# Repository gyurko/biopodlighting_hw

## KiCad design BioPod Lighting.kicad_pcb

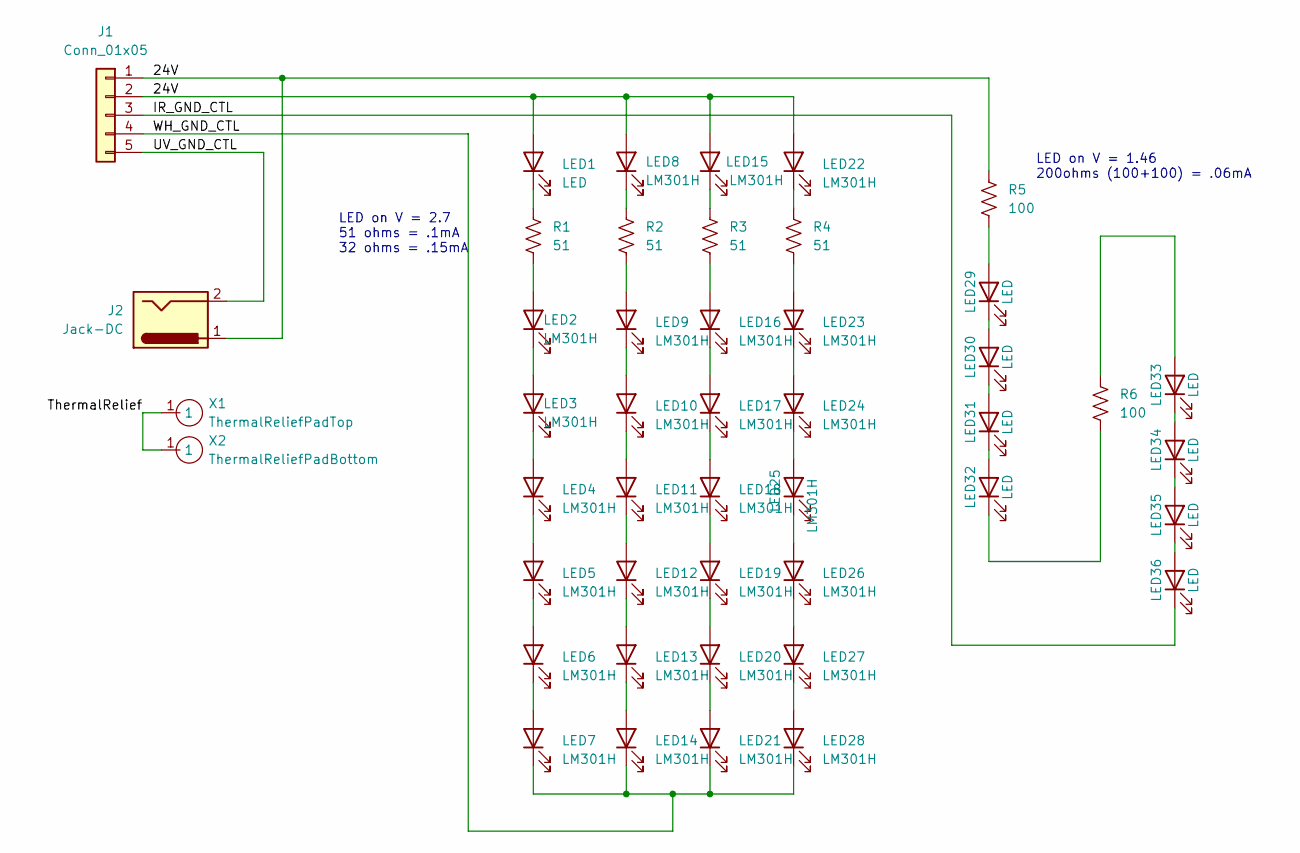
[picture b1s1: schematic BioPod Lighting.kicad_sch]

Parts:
J1: Conn_01x05; 5PinLightConnector
J2: Jack-DC; DisplayBoardDCJack
LED1: LED; LM301H_LED
LED2, LED3, LED4, LED5, LED6, LED7, LED8, LED9, LED10, LED11, LED12, LED13, LED14, LED15, LED16, LED17, LED18, LED19, LED20, LED21, LED22, LED23, LED24, LED25, LED26, LED27, LED28: LM301H; LM301H_LED
LED29, LED30, LED31, LED32, LED33, LED34, LED35, LED36: LED; SFH-4258_LED
R1, R2, R3, R4: 51; R_2512_6332Metric_Pad1.40x3.35mm_HandSolder
R5, R6: 100; R_2512_6332Metric_Pad1.40x3.35mm_HandSolder
X1: ThermalReliefPadTop; ThermalReliefWithMask
X2: ThermalReliefPadBottom; ThermalReliefNoMask

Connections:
/24V: J1.1, J1.2, J2.1, LED1.2 (A), LED8.2 (A), LED15.2 (A), LED22.2 (A), R5.1
/IR_GND_CTL: J1.3, LED36.1 (K)
/ThermalRelief: X1.1, X2.1
/UV_GND_CTL: J1.5, J2.2
/WH_GND_CTL: J1.4, LED7.1 (K), LED14.1 (K), LED21.1 (K), LED28.1 (K)
unnamed: LED1.1 (K), R1.1
unnamed: LED2.1 (K), LED3.2 (A)
unnamed: LED2.2 (A), R1.2
unnamed: LED3.1 (K), LED4.2 (A)
unnamed: LED4.1 (K), LED5.2 (A)
unnamed: LED5.1 (K), LED6.2 (A)
unnamed: LED6.1 (K), LED7.2 (A)
unnamed: LED8.1 (K), R2.1
unnamed: LED9.2 (A), R2.2
unnamed: LED10.1 (K), LED11.2 (A)
unnamed: LED9.1 (K), LED10.2 (A)
unnamed: LED11.1 (K), LED12.2 (A)
unnamed: LED12.1 (K), LED13.2 (A)
unnamed: LED13.1 (K), LED14.2 (A)
unnamed: LED15.1 (K), R3.1
unnamed: LED16.1 (K), LED17.2 (A)
unnamed: LED16.2 (A), R3.2
unnamed: LED17.1 (K), LED18.2 (A)
unnamed: LED18.1 (K), LED19.2 (A)
unnamed: LED19.1 (K), LED20.2 (A)
unnamed: LED20.1 (K), LED21.2 (A)
unnamed: LED22.1 (K), R4.1
unnamed: LED23.1 (K), LED24.2 (A)
unnamed: LED23.2 (A), R4.2
unnamed: LED24.1 (K), LED25.2 (A)
unnamed: LED25.1 (K), LED26.2 (A)
unnamed: LED26.1 (K), LED27.2 (A)
unnamed: LED27.1 (K), LED28.2 (A)
unnamed: LED29.1 (K), LED30.2 (A)
unnamed: LED29.2 (A), R5.2
unnamed: LED30.1 (K), LED31.2 (A)
unnamed: LED31.1 (K), LED32.2 (A)
unnamed: LED32.1 (K), R6.2
unnamed: LED33.1 (K), LED34.2 (A)
unnamed: LED33.2 (A), R6.1
unnamed: LED34.1 (K), LED35.2 (A)
unnamed: LED35.1 (K), LED36.2 (A)

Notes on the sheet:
LED on V = 1.46 200ohms (100+100) = .06mA
LED on V = 2.7 51 ohms = .1mA 32 ohms = .15mA

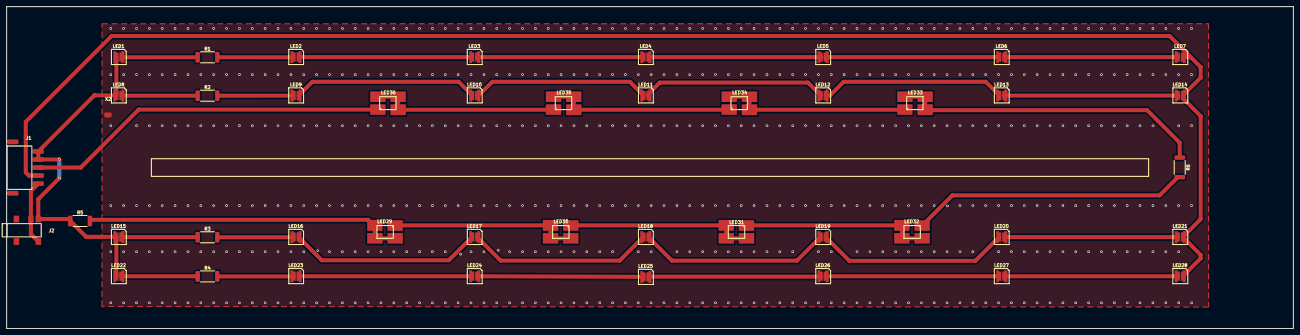
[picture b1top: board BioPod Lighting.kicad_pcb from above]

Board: 2 copper layers, 400.1 x 100.1 mm, 46 parts (1 on the bottom side), 42 nets.
